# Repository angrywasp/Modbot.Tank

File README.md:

# Modbot.Tank
Project to build an RC tank based on the Modbot system

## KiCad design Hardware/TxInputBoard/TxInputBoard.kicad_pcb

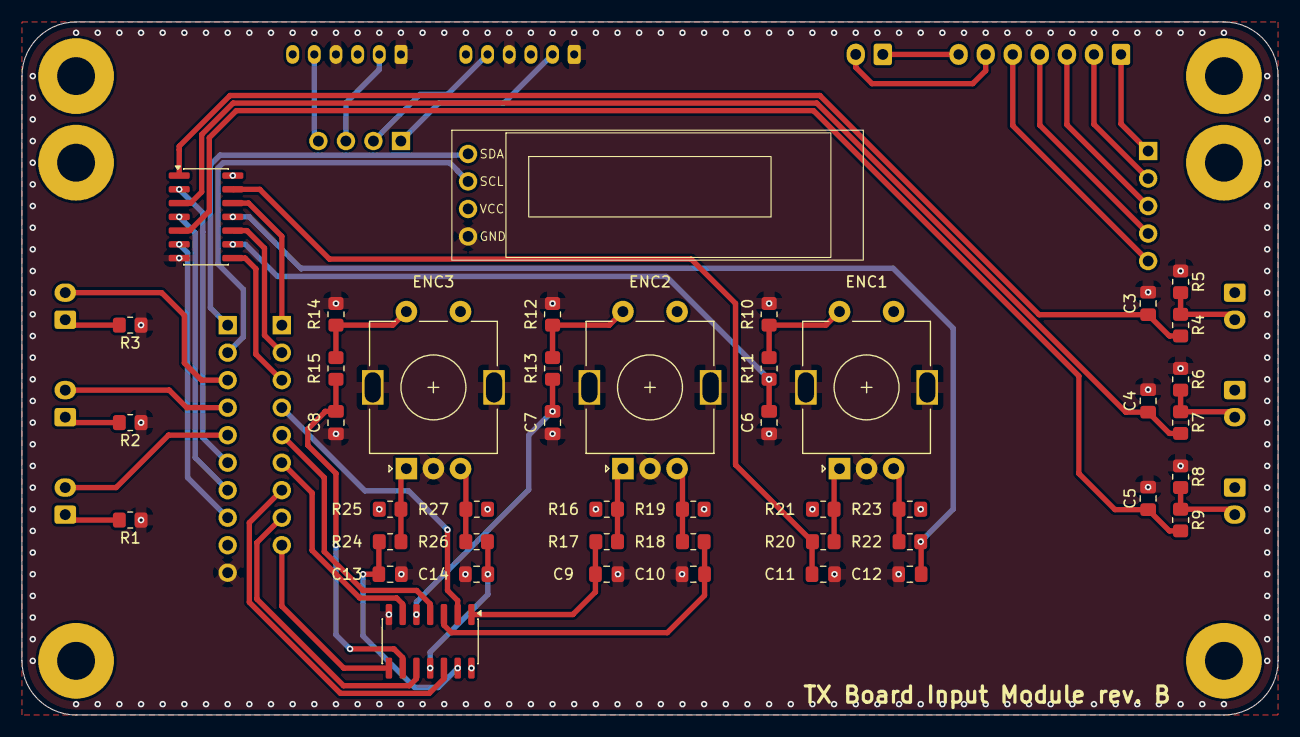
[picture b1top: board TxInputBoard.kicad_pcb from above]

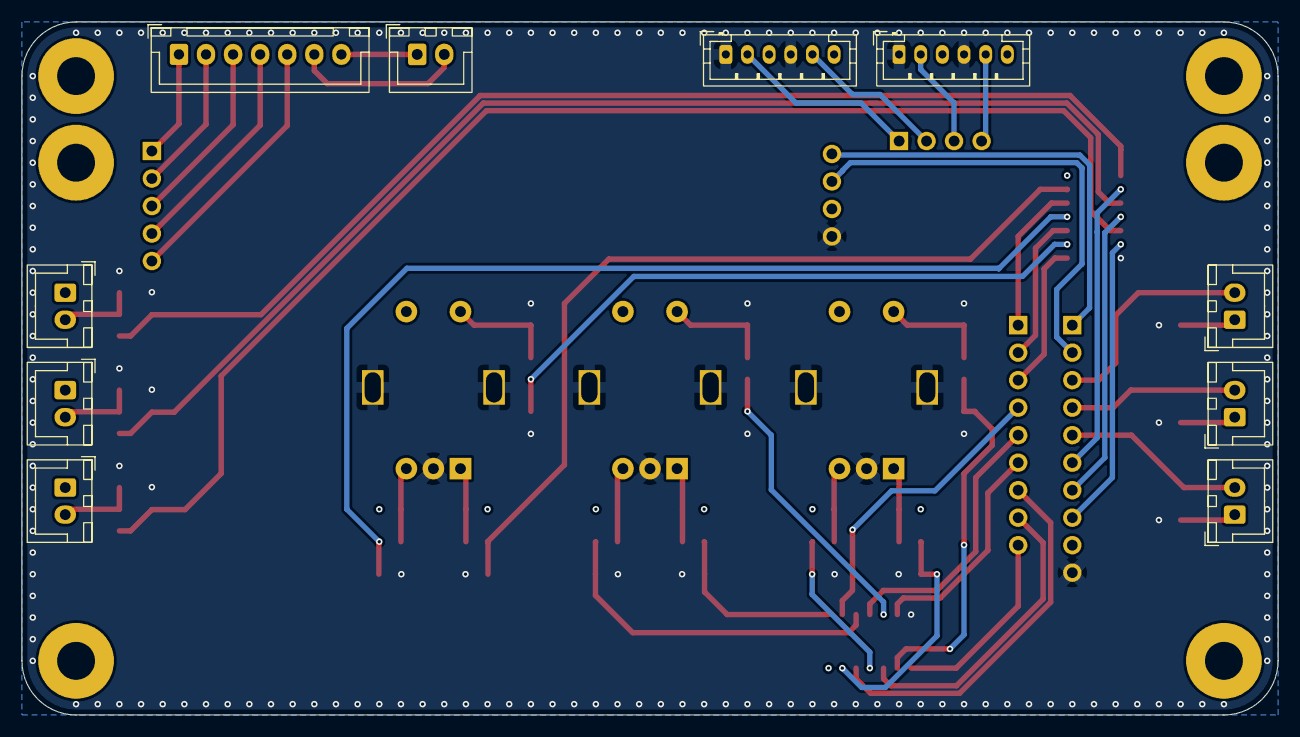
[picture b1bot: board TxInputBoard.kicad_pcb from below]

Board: 4 copper layers, 116.0 x 64.0 mm, 56 parts (11 on the bottom side), 57 nets.

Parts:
C3, C4, C5, C6, C7, C8, C9, C10, C11, C12, C13, C14: 0.1uF; C_0805_2012Metric_Pad1.18x1.45mm_HandSolder
ENC1, ENC2, ENC3: RotaryEncoder_Switch_MP; RotaryEncoder_Alps_EC11E-Switch_Vertical_H20mm
J4: L Joy; JST_PH_B6B-PH-K_1x06_P2.00mm_Vertical
J5: R Joy; JST_PH_B6B-PH-K_1x06_P2.00mm_Vertical
J8: OLED; SSD1306_OLED_128x32
JSwitch1: Conn_01x02; JST_XH_B2B-XH-A_1x02_P2.50mm_Vertical
L1, L2, L3: Green; JST_XH_B2B-XH-A_1x02_P2.50mm_Vertical
R1, R2, R3: 330; R_0805_2012Metric_Pad1.20x1.40mm_HandSolder
R4, R7, R9, R11, R13, R15: 1k; R_0805_2012Metric_Pad1.20x1.40mm_HandSolder
R5, R6, R8, R10, R12, R14, R16, R17, R18, R19, R20, R21, R22, R23, R24, R25, R26, R27: 10k; R_0805_2012Metric_Pad1.20x1.40mm_HandSolder
SW1, SW2, SW3: SW_SPST; JST_XH_B2B-XH-A_1x02_P2.50mm_Vertical
U1, U2: 74HC14; SO-14_3.9x8.65mm_P1.27mm
U3: MCP73831_18650Charger; JST_XH_B7B-XH-A_1x07_P2.50mm_Vertical
U4: MiniTx; TXBoardMini

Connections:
+3.3V: ENC1.S1, ENC2.S1, ENC3.S1, J4.3, J4.6, J5.3, J5.6, J8.3, R16.2, R19.2, R21.2, R23.2, R25.2, R27.2, SW1.1 (A), SW2.1 (A), SW3.1 (A), U1.14 (VCC), U2.14 (VCC), U4.18 (3v3)
CMP: U3.3 (CMP), U4.22 (CMP)
ENC1_A: U1.12, U4.1 (E1A)
ENC1_B: U1.10, U4.2 (E1B)
ENC1_SW: U1.8, U4.3 (E1SW)
ENC2_A: U2.2, U4.4 (E2A)
ENC2_B: U2.4, U4.5 (E2B)
ENC2_SW: U2.6, U4.6 (E2SW)
ENC3_A: U2.12, U4.7 (E3A)
ENC3_B: U2.10, U4.8 (E3B)
ENC3_SW: U2.8, U4.9 (E3SW)
GND: C3.2, C4.2, C5.2, C6.2, C7.2, C8.2, C9.2, C10.2, C11.2, C12.2, C13.2, C14.2, ENC1.C, ENC1.MP, ENC2.C, ENC2.MP, ENC3.C, ENC3.MP, J4.1, J4.4, J5.1, J5.4, J8.4, R1.1, R2.1, R3.1, R5.1, R6.1, R8.1, R10.1, R12.1, R14.1, U1.7 (GND), U2.7 (GND), U4.19 (GND)
IN+: U3.1 (IN+), U4.20 (IN+)
IN-: U3.2 (IN-), U4.21 (IN-)
LED_1: L1.2 (A), U4.14 (LED1)
LED_2: L2.2 (A), U4.13 (LED2)
LED_3: L3.2 (A), U4.12 (LED3)
LJOY1: J4.2, U4.25 (A1)
LJOY2: J4.5, U4.26 (A2)
unnamed: C3.1, R4.2, U1.1
unnamed: C4.1, R7.2, U1.3
unnamed: C5.1, R9.2, U1.5
unnamed: C6.1, R11.2, U1.9
unnamed: C7.1, R13.2, U2.5
unnamed: C8.1, R15.2, U2.9
unnamed: C9.1, R17.2, U2.1
unnamed: C10.1, R18.2, U2.3
unnamed: C11.1, R20.2, U1.13
unnamed: C12.1, R22.2, U1.11
unnamed: C13.1, R24.2, U2.13
unnamed: C14.1, R26.2, U2.11
unnamed: ENC1.A, R20.1, R21.1
unnamed: ENC1.B, R22.1, R23.1
unnamed: ENC1.S2, R10.2, R11.1
unnamed: ENC2.A, R16.1, R17.1
unnamed: ENC2.B, R18.1, R19.1
unnamed: ENC2.S2, R12.2, R13.1
unnamed: ENC3.A, R24.1, R25.1
unnamed: ENC3.B, R26.1, R27.1
unnamed: ENC3.S2, R14.2, R15.1
unnamed: JSwitch1.1, U3.7 (SW)
unnamed: JSwitch1.2, U3.6 (SW)
unnamed: L1.1 (K), R1.2
unnamed: L2.1 (K), R2.2
unnamed: L3.1 (K), R3.2
unnamed: R4.1, R5.2, SW1.2 (B)
unnamed: R6.2, R7.1, SW2.2 (B)
unnamed: R8.2, R9.1, SW3.2 (B)
OLED_SCL: J8.2, U4.11 (OLED_SCL)
OLED_SDA: J8.1, U4.10 (OLED_SDA)
OUT+: U3.5 (OUT+), U4.24 (OUT+)
OUT-: U3.4 (OUT-), U4.23 (OUT-)
RJOY1: J5.2, U4.27 (A3)
RJOY2: J5.5, U4.28 (A4)
SW1: U1.2, U4.15 (SW1)
SW2: U1.4, U4.16 (SW2)
SW3: U1.6, U4.17 (SW3)

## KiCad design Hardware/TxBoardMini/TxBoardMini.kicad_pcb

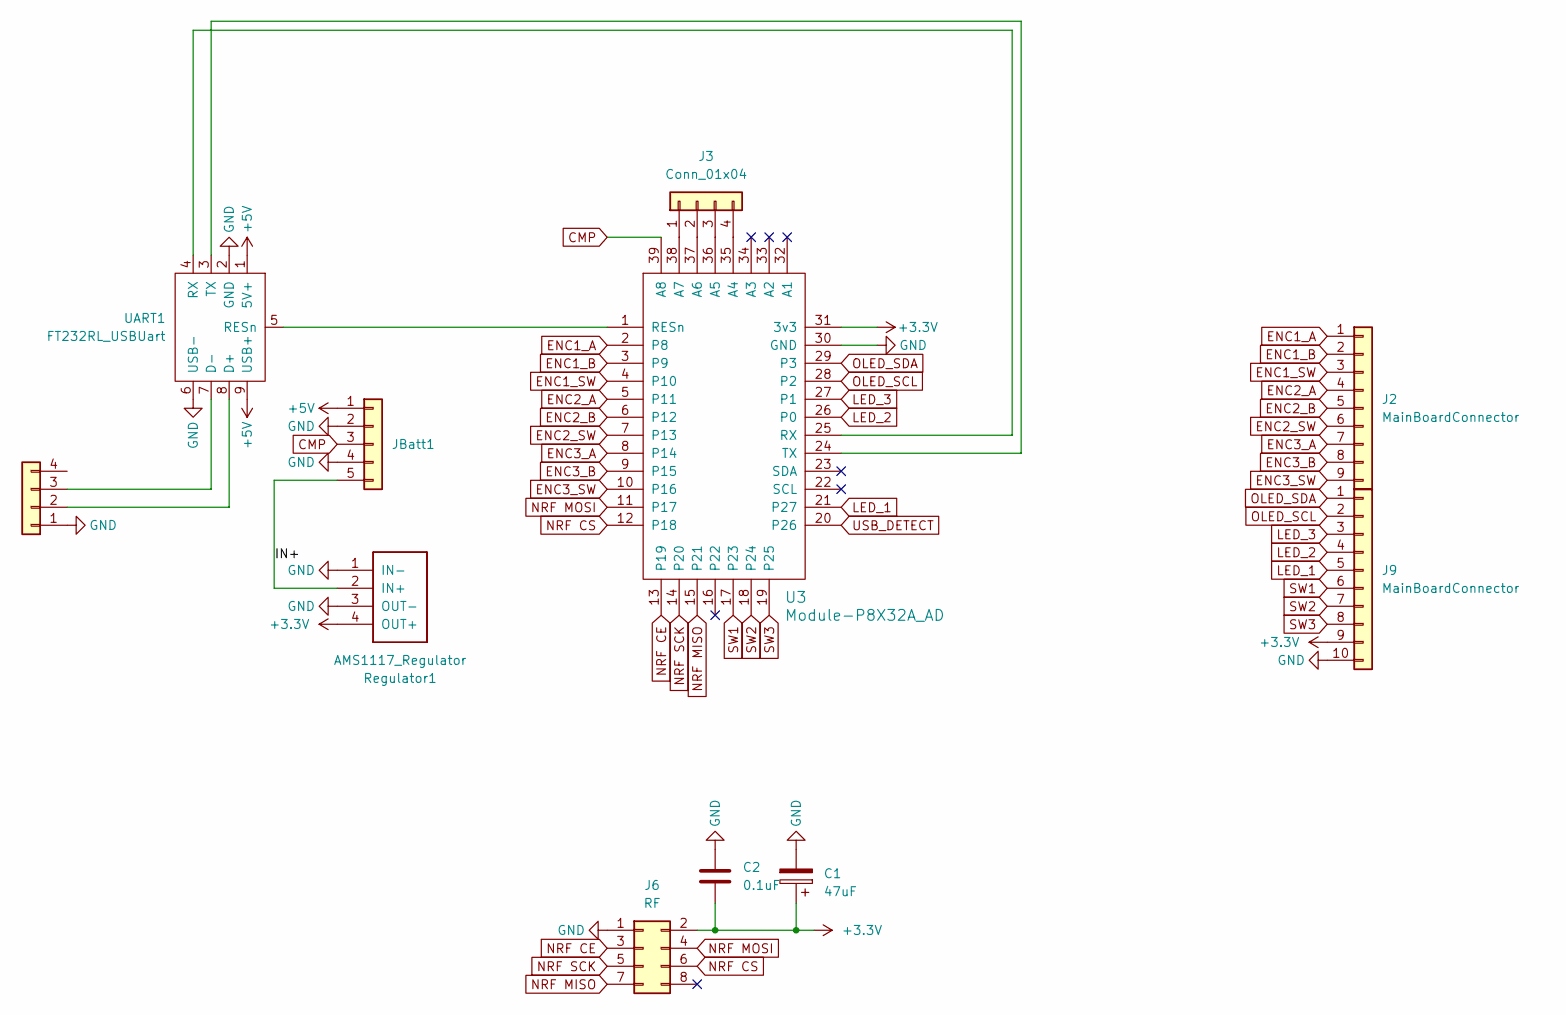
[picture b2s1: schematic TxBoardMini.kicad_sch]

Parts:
C1: 47uF; CP_Elec_5x5.3
C2: 0.1uF; C_0805_2012Metric_Pad1.18x1.45mm_HandSolder
J1: USB; JST_PH_B4B-PH-K_1x04_P2.00mm_Vertical
J2: MainBoardConnector; PinHeader_1x09_P2.54mm_Vertical
J3: Conn_01x04; PinHeader_1x04_P2.54mm_Vertical
J6: RF; PinHeader_2x04_P2.54mm_Vertical
J9: MainBoardConnector; PinHeader_1x10_P2.54mm_Vertical
JBatt1: Conn_01x05; PinHeader_1x05_P2.54mm_Vertical
Regulator1: AMS1117_Regulator; Module-SOT-223_TO-252-3_Regulator
U3: Module-P8X32A_AD
UART1: FT232RL_USBUart; Module-FT232RL_USBUart

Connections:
+3.3V: C1.1, C2.2, J6.2, J9.9, Regulator1.4 (OUT+), U3.31 (3v3)
+5V: JBatt1.1, UART1.1 (5V+), UART1.9 (USB+)
/IN+: JBatt1.5, Regulator1.2 (IN+)
CMP: JBatt1.3, U3.39 (A8)
ENC1_A: J2.1, U3.2 (P8)
ENC1_B: J2.2, U3.3 (P9)
ENC1_SW: J2.3, U3.4 (P10)
ENC2_A: J2.4, U3.5 (P11)
ENC2_B: J2.5, U3.6 (P12)
ENC2_SW: J2.6, U3.7 (P13)
ENC3_A: J2.7, U3.8 (P14)
ENC3_B: J2.8, U3.9 (P15)
ENC3_SW: J2.9, U3.10 (P16)
GND: C1.2, C2.1, J1.1, J6.1, J9.10, JBatt1.2, JBatt1.4, Regulator1.1 (IN-), Regulator1.3 (OUT-), U3.30 (GND), UART1.2 (GND), UART1.6 (USB-)
LED_1: J9.5, U3.21 (P27)
LED_2: J9.4, U3.26 (P0)
LED_3: J9.3, U3.27 (P1)
NRF CE: J6.3, U3.13 (P19)
NRF CS: J6.6, U3.12 (P18)
NRF MISO: J6.7, U3.15 (P21)
NRF MOSI: J6.4, U3.11 (P17)
NRF SCK: J6.5, U3.14 (P20)
unnamed: J1.2, UART1.8 (D+)
unnamed: J1.3, UART1.7 (D-)
unnamed: J3.1, U3.38 (A7)
unnamed: J3.2, U3.37 (A6)
unnamed: J3.3, U3.36 (A5)
unnamed: J3.4, U3.35 (A4)
unnamed: U3.1 (RESn), UART1.5 (RESn)
unnamed: U3.25 (RX), UART1.4 (RX)
unnamed: U3.24 (TX), UART1.3 (TX)
OLED_SCL: J9.2, U3.28 (P2)
OLED_SDA: J9.1, U3.29 (P3)
SW1: J9.6, U3.17 (P23)
SW2: J9.7, U3.18 (P24)
SW3: J9.8, U3.19 (P25)
USB_DETECT: U3.20 (P26)

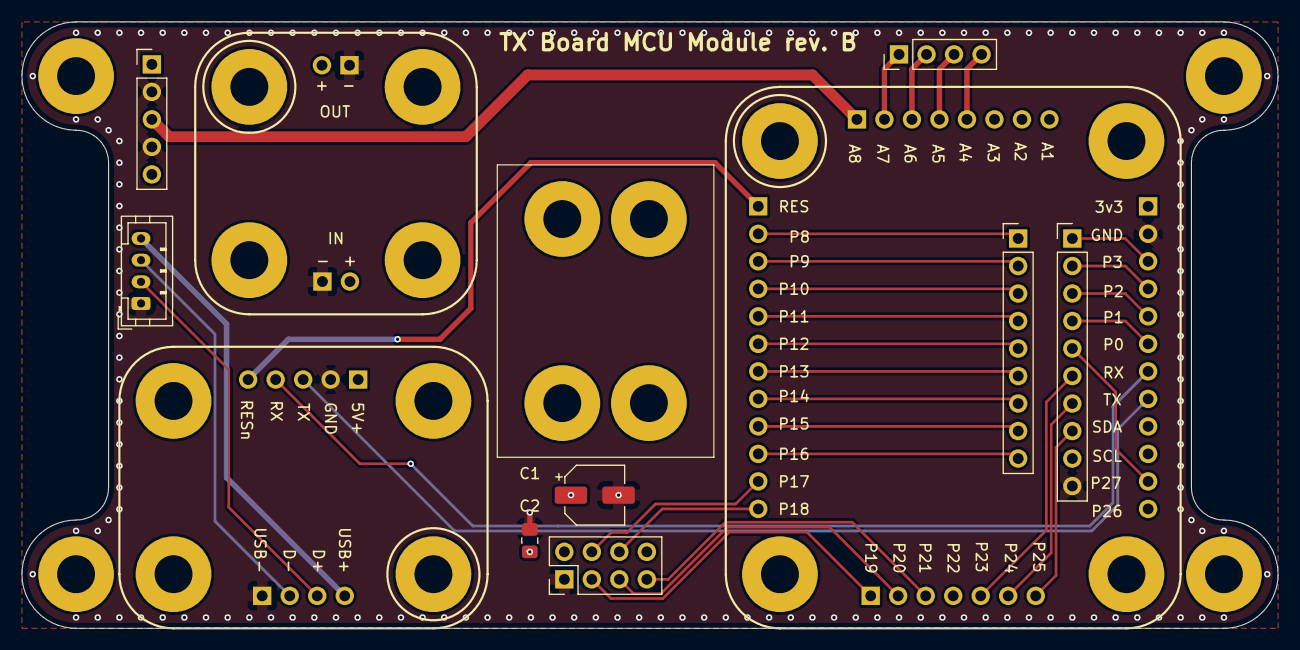
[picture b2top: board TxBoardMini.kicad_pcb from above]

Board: 4 copper layers, 116.0 x 56.0 mm, 11 parts (0 on the bottom side), 36 nets.

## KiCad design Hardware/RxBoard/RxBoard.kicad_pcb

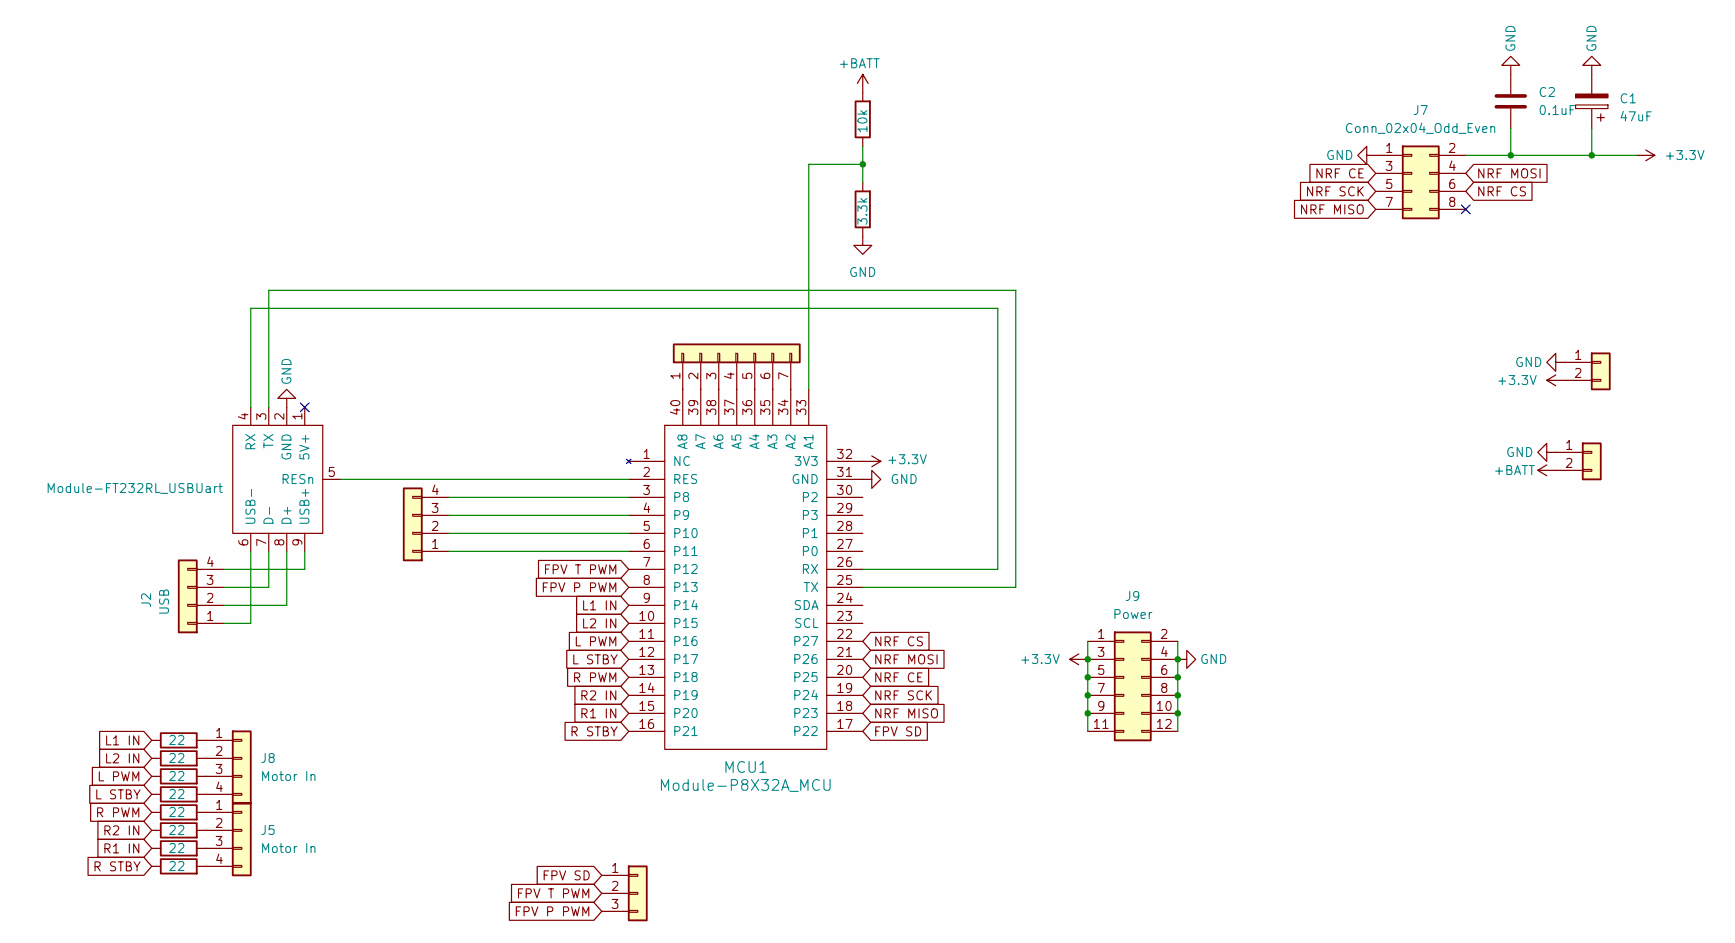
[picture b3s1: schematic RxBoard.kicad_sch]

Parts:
C1: 47uF; CP_Elec_5x5.3
C2: 0.1uF; C_0805_2012Metric_Pad1.18x1.45mm_HandSolder
J1: Conn_01x04; JST_XH_B3B-XH-A_1x03_P2.50mm_Vertical
J2: USB; JST_PH_B4B-PH-K_1x04_P2.00mm_Vertical
J3: Conn_01x09; PinHeader_1x04_P2.54mm_Vertical
J4: Conn_01x08; PinHeader_1x07_P2.54mm_Vertical
J5, J8: Motor In; JST_XH_B4B-XH-A_1x04_P2.50mm_Vertical
J7: Conn_02x04_Odd_Even; PinHeader_2x04_P2.54mm_Vertical
J9: Power; PinHeader_2x06_P2.54mm_Vertical
J10, J11: Conn_01x02; AMASS_XT30UPB-M_1x02_P5.0mm_Vertical
MCU1: Module-P8X32A_MCU
R1, R2, R3, R4, R5, R6, R7, R8: 22; R_0805_2012Metric_Pad1.20x1.40mm_HandSolder
R9: 10k; R_0805_2012Metric_Pad1.20x1.40mm_HandSolder
R10: 3.3k; R_0805_2012Metric_Pad1.20x1.40mm_HandSolder
UART1: Module-FT232RL_USBUart

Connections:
+3.3V: C1.1, C2.2, J7.2, J9.1, J9.3, J9.5, J9.7, J9.9, J9.11, J11.2, MCU1.32 (3V3)
+BATT: J10.2, R9.2
FPV P PWM: J1.3, MCU1.8 (P13)
FPV SD: J1.1, MCU1.17 (P22)
FPV T PWM: J1.2, MCU1.7 (P12)
GND: C1.2, C2.1, J7.1, J9.2, J9.4, J9.6, J9.8, J9.10, J9.12, J10.1, J11.1, MCU1.31 (GND), R10.1, UART1.2 (GND)
L1 IN: MCU1.9 (P14), R1.1
L2 IN: MCU1.10 (P15), R2.1
L PWM: MCU1.11 (P16), R3.1
L STBY: MCU1.12 (P17), R4.1
NRF CE: J7.3, MCU1.20 (P25)
NRF CS: J7.6, MCU1.22 (P27)
NRF MISO: J7.7, MCU1.18 (P23)
NRF MOSI: J7.4, MCU1.21 (P26)
NRF SCK: J7.5, MCU1.19 (P24)
unnamed: J2.1, UART1.6 (USB-)
unnamed: J2.2, UART1.8 (D+)
unnamed: J2.3, UART1.7 (D-)
unnamed: J2.4, UART1.9 (USB+)
unnamed: J3.1, MCU1.6 (P11)
unnamed: J3.2, MCU1.5 (P10)
unnamed: J3.3, MCU1.4 (P9)
unnamed: J3.4, MCU1.3 (P8)
unnamed: J4.1, MCU1.40 (A8)
unnamed: J4.2, MCU1.39 (A7)
unnamed: J4.3, MCU1.38 (A6)
unnamed: J4.4, MCU1.37 (A5)
unnamed: J4.5, MCU1.36 (A4)
unnamed: J4.6, MCU1.35 (A3)
unnamed: J4.7, MCU1.34 (A2)
unnamed: J5.1, R5.2
unnamed: J5.2, R6.2
unnamed: J5.3, R7.2
unnamed: J5.4, R8.2
unnamed: J8.1, R1.2
unnamed: J8.2, R2.2
unnamed: J8.3, R3.2
unnamed: J8.4, R4.2
unnamed: MCU1.33 (A1), R9.1, R10.2
unnamed: MCU1.2 (RES), UART1.5 (RESn)
unnamed: MCU1.26 (RX), UART1.4 (RX)
unnamed: MCU1.25 (TX), UART1.3 (TX)
R1 IN: MCU1.15 (P20), R7.1
R2 IN: MCU1.14 (P19), R6.1
R PWM: MCU1.13 (P18), R5.1
R STBY: MCU1.16 (P21), R8.1

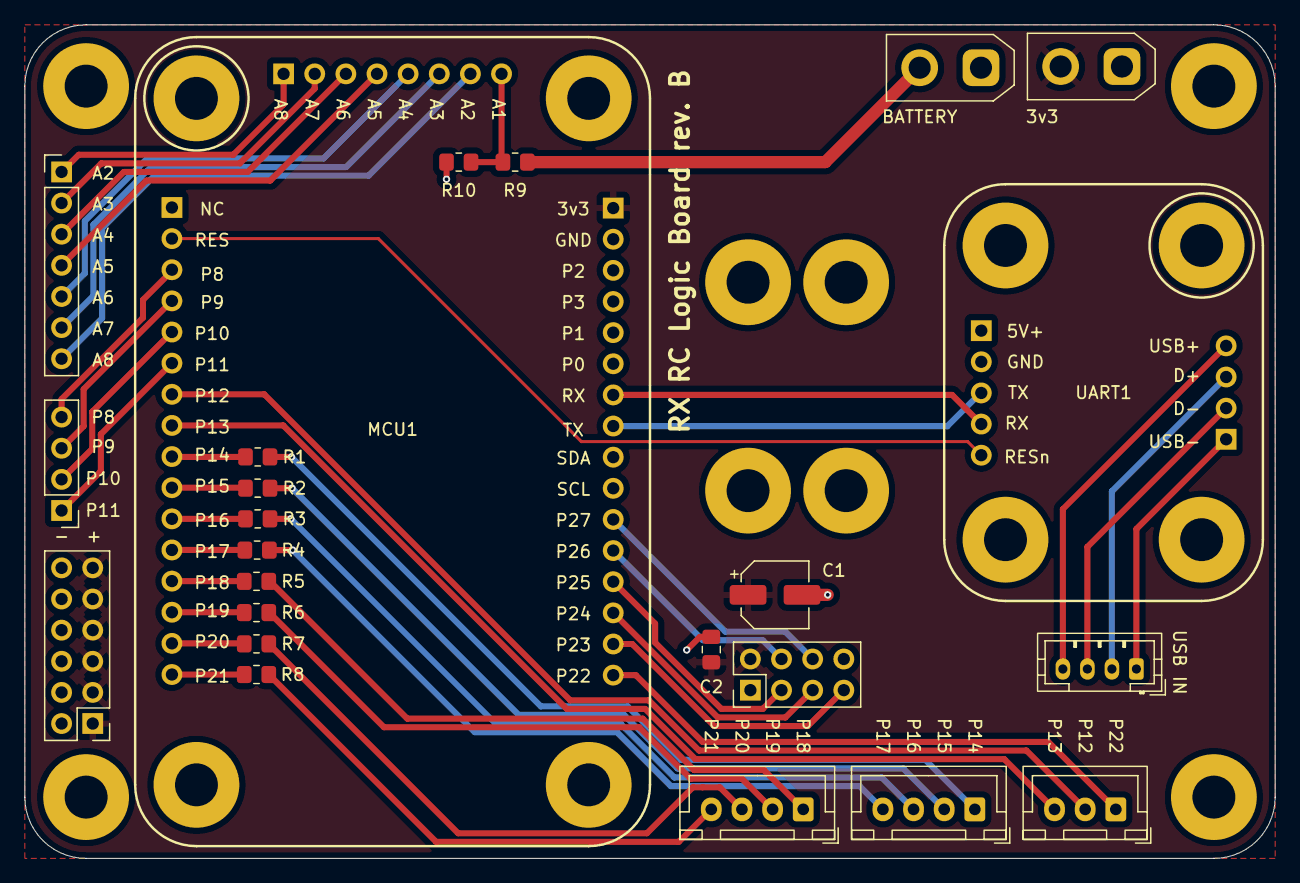
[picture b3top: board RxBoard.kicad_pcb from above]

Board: 2 copper layers, 102.0 x 68.0 mm, 24 parts (0 on the bottom side), 46 nets.

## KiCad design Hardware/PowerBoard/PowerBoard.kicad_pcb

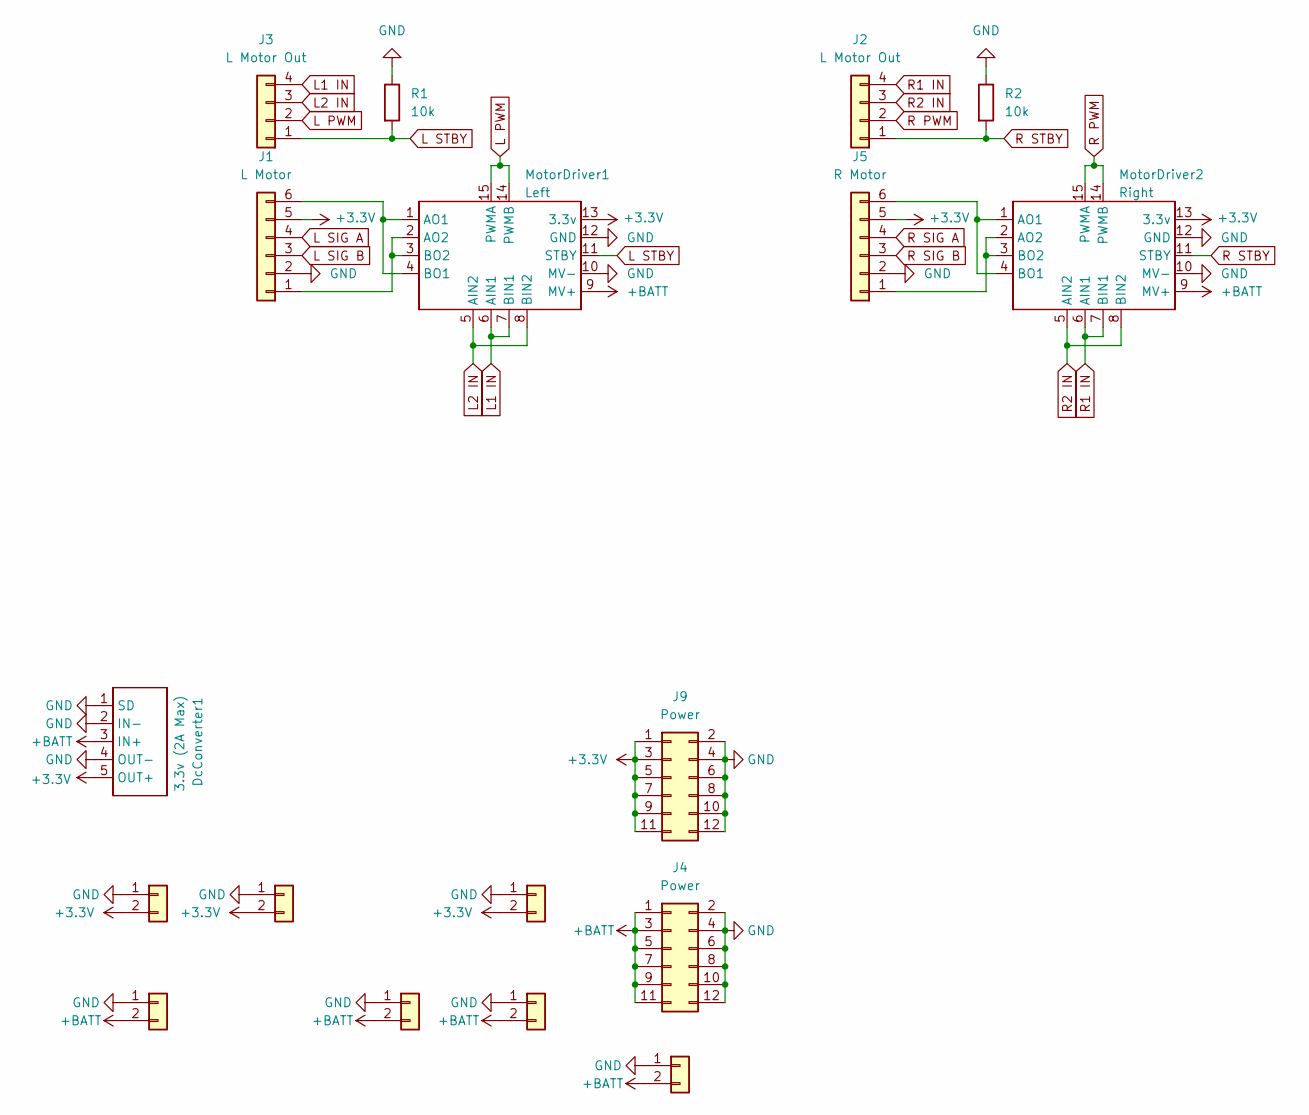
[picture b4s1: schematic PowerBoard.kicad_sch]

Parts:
DcConverter1: 3.3v (2A Max); Module-AP1509_DcConverter
J1: L Motor; JST_PH_B6B-PH-K_1x06_P2.00mm_Vertical
J2, J3: L Motor Out; JST_XH_B4B-XH-A_1x04_P2.50mm_Vertical
J4, J9: Power; PinHeader_2x06_P2.54mm_Vertical
J5: R Motor; JST_PH_B6B-PH-K_1x06_P2.00mm_Vertical
J7, J10, J12, J17, J18, J20: Conn_01x02; AMASS_XT30UPB-F_1x02_P5.0mm_Vertical
J8: Conn_01x02; AMASS_XT60PW-M_1x02_P7.20mm_Horizontal
MotorDriver1: Left; Module-TB6612FNG_MotorDriver
MotorDriver2: Right; Module-TB6612FNG_MotorDriver
R1, R2: 10k; R_0805_2012Metric_Pad1.20x1.40mm_HandSolder

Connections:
+3.3V: DcConverter1.5 (OUT+), J1.5, J5.5, J7.2, J9.1, J9.3, J9.5, J9.7, J9.9, J9.11, J10.2, J18.2, MotorDriver1.13 (3.3v), MotorDriver2.13 (3.3v)
+BATT: DcConverter1.3 (IN+), J4.1, J4.3, J4.5, J4.7, J4.9, J4.11, J8.2, J12.2, J17.2, J20.2, MotorDriver1.9 (MV+), MotorDriver2.9 (MV+)
GND: DcConverter1.1 (SD), DcConverter1.2 (IN-), DcConverter1.4 (OUT-), J1.2, J4.2, J4.4, J4.6, J4.8, J4.10, J4.12, J5.2, J7.1, J8.1, J9.2, J9.4, J9.6, J9.8, J9.10, J9.12, J10.1, J12.1, J17.1, J18.1, J20.1, MotorDriver1.10 (MV-), MotorDriver1.12 (GND), MotorDriver2.10 (MV-), MotorDriver2.12 (GND), R1.1, R2.1
L1 IN: J3.4, MotorDriver1.6 (AIN1), MotorDriver1.7 (BIN1)
L2 IN: J3.3, MotorDriver1.5 (AIN2), MotorDriver1.8 (BIN2)
L PWM: J3.2, MotorDriver1.14 (PWMB), MotorDriver1.15 (PWMA)
L SIG A: J1.4
L SIG B: J1.3
L STBY: J3.1, MotorDriver1.11 (STBY), R1.2
unnamed: J1.1, MotorDriver1.2 (AO2), MotorDriver1.3 (BO2)
unnamed: J1.6, MotorDriver1.1 (AO1), MotorDriver1.4 (BO1)
unnamed: J5.1, MotorDriver2.2 (AO2), MotorDriver2.3 (BO2)
unnamed: J5.6, MotorDriver2.1 (AO1), MotorDriver2.4 (BO1)
R1 IN: J2.4, MotorDriver2.6 (AIN1), MotorDriver2.7 (BIN1)
R2 IN: J2.3, MotorDriver2.5 (AIN2), MotorDriver2.8 (BIN2)
R PWM: J2.2, MotorDriver2.14 (PWMB), MotorDriver2.15 (PWMA)
R SIG A: J5.4
R SIG B: J5.3
R STBY: J2.1, MotorDriver2.11 (STBY), R2.2

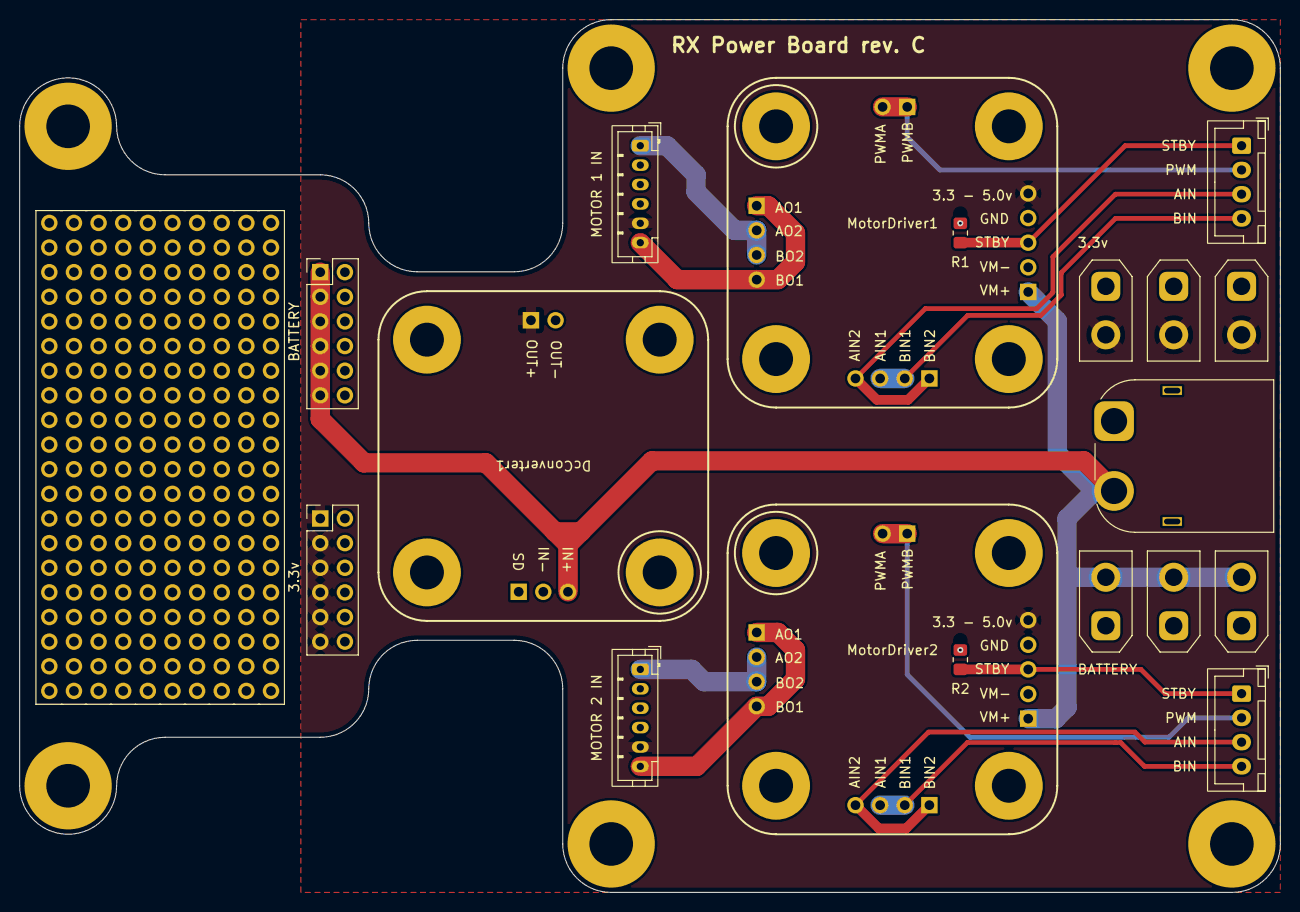
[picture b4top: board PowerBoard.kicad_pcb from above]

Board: 2 copper layers, 130.0 x 90.0 mm, 18 parts (0 on the bottom side), 15 nets.

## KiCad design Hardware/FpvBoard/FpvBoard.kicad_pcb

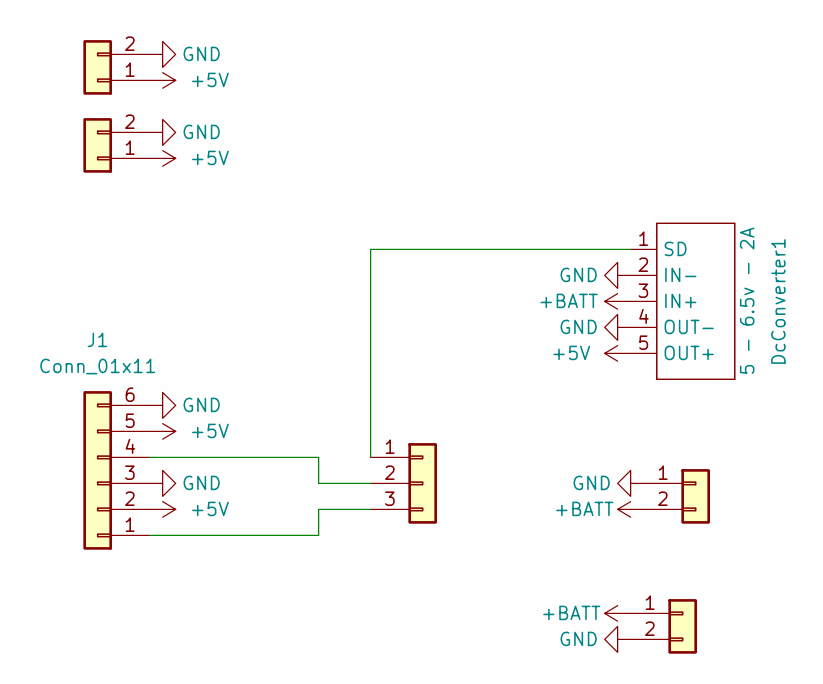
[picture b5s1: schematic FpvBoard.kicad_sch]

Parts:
DcConverter1: 5 - 6.5v - 2A; Module-AP1509_DcConverter
J1: Conn_01x11; PinHeader_1x06_P2.54mm_Vertical
J2: Conn_01x03; JST_XH_B3B-XH-A_1x03_P2.50mm_Vertical
J3, J4, J5: Conn_01x02; JST_XH_B2B-XH-A_1x02_P2.50mm_Vertical
J8: Conn_01x02; AMASS_XT30UPB-M_1x02_P5.0mm_Vertical

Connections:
+5V: DcConverter1.5 (OUT+), J1.2, J1.5, J4.1, J5.1
+BATT: DcConverter1.3 (IN+), J3.1, J8.2
GND: DcConverter1.2 (IN-), DcConverter1.4 (OUT-), J1.3, J1.6, J3.2, J4.2, J5.2, J8.1
unnamed: DcConverter1.1 (SD), J2.1
unnamed: J1.1, J2.3
unnamed: J1.4, J2.2

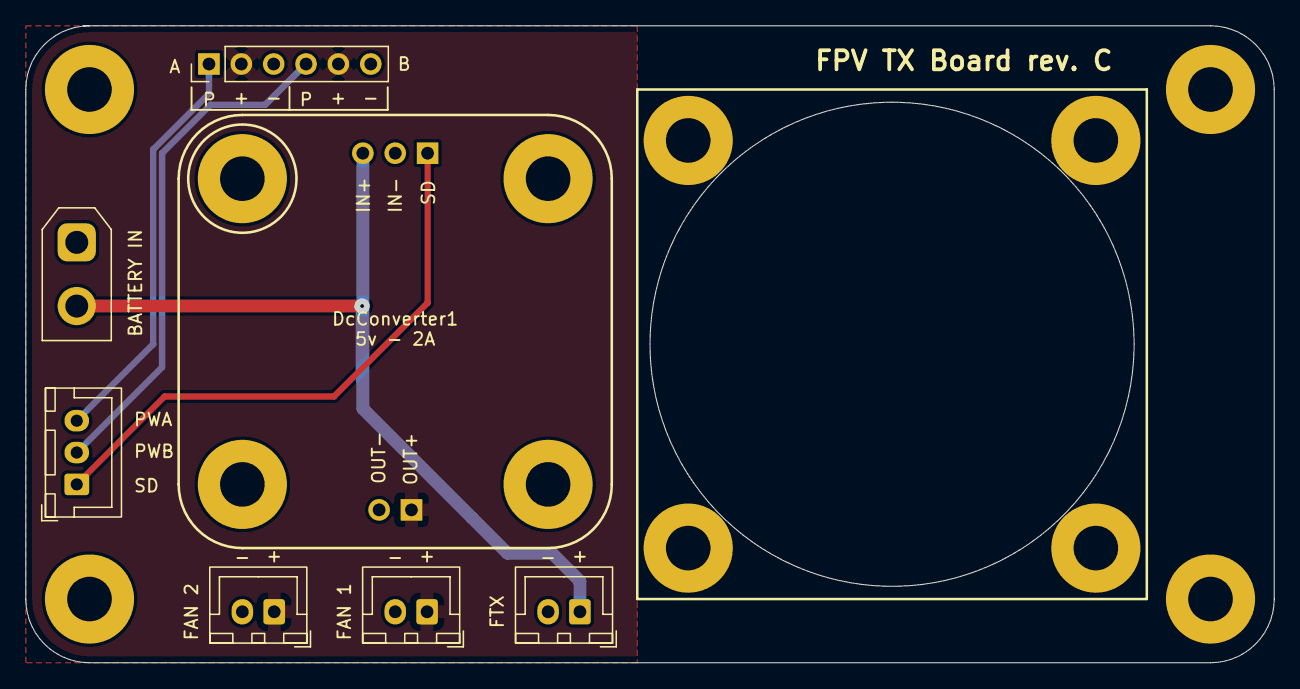
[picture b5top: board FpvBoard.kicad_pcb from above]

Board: 2 copper layers, 98.0 x 50.0 mm, 7 parts (0 on the bottom side), 6 nets.

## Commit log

2026-05-19 VS Code settings updates
2026-05-19 Work on build scripts
2026-05-19 Build success
2026-05-25 Hardware cleanup
